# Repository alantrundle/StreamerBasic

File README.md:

# ESP32 Audio Streaming & Playback Platform

An all-in-one **ESP32-based audio platform** providing HTTP streaming, on-device decoding, and multiple audio outputs with a full graphical UI.  
Designed for **ESP32-WROVER (8MB PSRAM)** and intended for use with a **custom PCB (v1.1)** or off-the-shelf modules.

---

## 📸 PCB – Prototype (v1.1)

**Left → Right:**  
Front view with LVGL UI • Player close-up • Angled top view • Rear view with Li-Po battery fitted

> ⚠️ **ESP32-WROVER with 8MB PSRAM is mandatory**  
> Bluetooth Classic (A2DP), audio buffers, and LVGL require PSRAM for stability.

---

## ✨ Key Features

- **Automatic MP3 & AAC codec detection** (header-level)
- **ID3v2 tag parsing**
  - Title, artist, album
  - JPEG album-art decoding
- **Bluetooth A2DP output**
  - Line-out & external sinks
  - Automatic reconnect logic
- **I2S audio output**
  - Developed using PCM5102 DAC
- **Dual-reader PCM ring buffer**
  - Independent A2DP & I2S consumption
- **LVGL graphical UI**
  - Capacitive touch support
  - ST7796 demo included
- **Transport controls**
  - Play / Pause / Stop
  - Next / Previous track

---

## 🧠 Architecture Overview

- HTTP audio streaming
- On-device MP3 / AAC decoding (Helix)
- Shared PCM buffer with dual read pointers
- Parallel audio output to:
  - Bluetooth A2DP
  - I2S DAC
- LVGL UI running primarily from PSRAM
- Designed around **FreeRTOS task separation**, flow-control, and buffer hysteresis

---

## 🖥 TFT Display Pinout (PCB v1.1 – ST7796, SPI)

The PCB v1.1 is wired for a **4″ ST7796 SPI TFT with capacitive touch**, sharing the SPI bus with the SD card.

> ⚠️ TFT and SD **share SPI lines**  
> Separate CS lines are mandatory and handled in firmware.

**4″ TFT Capacitive Touch Display (ST7796)**  
- https://www.aliexpress.com/item/1005006698127763.html

---

### 📌 ESP32 ↔ TFT Connections

| TFT Signal | ESP32 GPIO | ESP32 Pin # | Notes |
|------------|------------|-------------|-------|
| **VCC** | 3.3 V | — | Display power |
| **GND** | GND | — | Ground |
| **CS** | GPIO 33 | **P8** | TFT Chip select |
| **RST** | GPIO 32 | **P7** | TFT reset |
| **DC/RS** | GPIO 27 | **P13** | TFT DC/RS |
| **MOSI** | GPIO 23 | **P37** | VSPI MOSI |
| **SCK** | GPIO 18 | **P30** | VSPI CLK |
| **BL** | GPIO 25 | **P10** | TFT Backlight - PWM capable |
| **MISO** | GPIO 34 | **P37** | VSPI MISO |

---

### ✋ Capacitive Touch Controller (I²C)

(FT6236 / GT911 class controller)

| Touch Signal | ESP32 GPIO | ESP32 Pin # | Notes |
|--------------|------------|-------------|-------|
| **SCL** | GPIO 22 | **P36** | I²C Clock |
| **RST** | GPIO 26 | **P11** | Touch reset |
| **SDA** | GPIO 21 | **P33** | I²C Data |
| **INT** | GPIO 39 | **P4** | Touch interrupt (input-only) |

---

### 💾 SD Card (Shared SPI Bus)

| SD Signal | ESP32 GPIO | ESP32 Pin # | Notes |
|-----------|------------|-------------|-------|
| **VCC** | 3.3 V | — | Power |
| **GND** | GND | — | Ground |
| **CS** | GPIO 5 | **P29** | SD Card Chip Select |
| **SCK** | GPIO 18 | **P30** | Shared VSPI Clock |
| **MOSI** | GPIO 23 | **P37** | Shared VSPI MOSI |
| **MISO** | GPIO 34 | **P5** | Shared VSPI MISO |

---

## 🔌 Expansion Header (PCB v1.1)

Unused GPIOs are exposed via an **Expansion Header** for future peripherals (encoders, buttons, sensors, GPIO).

| Expansion | ESP32 GPIO | ESP32 Pin # | Notes |
|-----------|------------|-------------|-------|
| **3.3V** | 3.3 V | — | Power Output |
| **GND** | GND | — | Ground |
| **SDA** | GPIO 21 | **P33** | I²C SDA (shared with Touch) |
| **SCL** | GPIO 22 | **P36** | I²C SCL (shared with Touch) |
| **SD_CS** | GPIO 5 | **P29** | GPIO if SD not used (strap pin – don’t drive at boot)|
| **GPIO 4** | GPIO 4 | **P26** | GPIO (strap behaviour – keep low/floating at boot)|
| **GPIO 15** | GPIO 15 | **P14** | GPIO (strap pin – must be LOW at boot) |
| **GPIO 19** | GPIO 19 | **P31** | GPIO |
| **GPIO 35** | GPIO 35 | **P6** | Input-only (ADC)|
| **GPIO 36** | GPIO 36 | **P3** | Input-only (ADC)|
| **3.3V** | 3.3 V | — | Power output |
| **GND** | GND | — | Ground |

---

### ⚠️ Electrical & Boot Notes

⚠️ Use with care
GPIO 4, 5 & 15 → boot strap pins (must not be driven during reset)
Must be LOW or floating at boot

GPIO 34 / 39 → input-only, no pullups

❌ Output not possible
GPIO 34–39

---

## ⚠️ Known Issues & Limitations

- **LVGL + Bluetooth + Wi-Fi are extremely DRAM-heavy**
  - LVGL buffers must reside mostly in PSRAM
  - Moving `lvbuf1` to DRAM can crash Wi-Fi + BT
  - Use 4 lines maximum
- **Dual buffering in PSRAM is slower**
  - Trade-off required for system stability
- **Wi-Fi coexistence instability**
  - Occasional crashes under heavy load
- **ESP-IDF versions**
  - Rolled back to **ESP32 core v6.4.0** for stability
  - Newer versions attempt BT sleep → A2DP instability
- **Bluetooth**
  - Seems stable

---

## 🧪 Current Testing Status

- Use stable branch for latest stable

- Use main branch for latest code. 

⚠️ main may be broken if I am in the process of making multi-day changes.

12/01/2026
- added Bluetooth Manager for Sink Devices
- added basic WiFi handler
- changed menu - added icons
- added icon pack to Playback 

---

## 🛠 To-Do

- Plex Media Server integration
- General bug fixes & cleanup
- Ogg Vorbis support
- Improved AAC decoding
- LVGL dual buffering in DRAM (if feasible)

---

## ✅ Pros

- Stable during extended playback
- Robust codec detection
- Clean separation of decode and output paths
- Scales well with PSRAM availability

---

## 📦 Recommended Development Kit (Without PCB)

### ESP32 Module

**ESP32-WROVER (8MB PSRAM + TF Card)**  
- https://www.aliexpress.com/item/32879370278.html

### Display

**4″ TFT Capacitive Touch Display (ST7796)**  
- https://www.aliexpress.com/item/1005006698127763.html

### Audio DAC

**PCM5102 I2S DAC**  
Stereo RCA + headphone / line-out  
- https://www.aliexpress.com/item/1005005352684938.html

---

## 📄 License

**Project status:** Active Development

**License:**  
Free for **personal, educational, and hobbyist use**.

**Commercial use is not permitted without explicit written permission from the author.**  
This includes (but is not limited to) commercial products, services, or redistributed hardware.

If you wish to use this project commercially, please contact the author via GitHub.

---

## 🙌 Acknowledgements

- ESP32 Arduino Core  
- LVGL Graphics Library  
- Helix Audio Codecs  

## 🙌 Development Software
- MacOS 15.5
- Visual Studio Code Version: 1.108.0 (Universal)
- PlatformIO Core Version: 6.1.18·Home 3.4.4
- EEZ Studio Version: 0.24.0
- KiCAD Version: 9.0.6 release build

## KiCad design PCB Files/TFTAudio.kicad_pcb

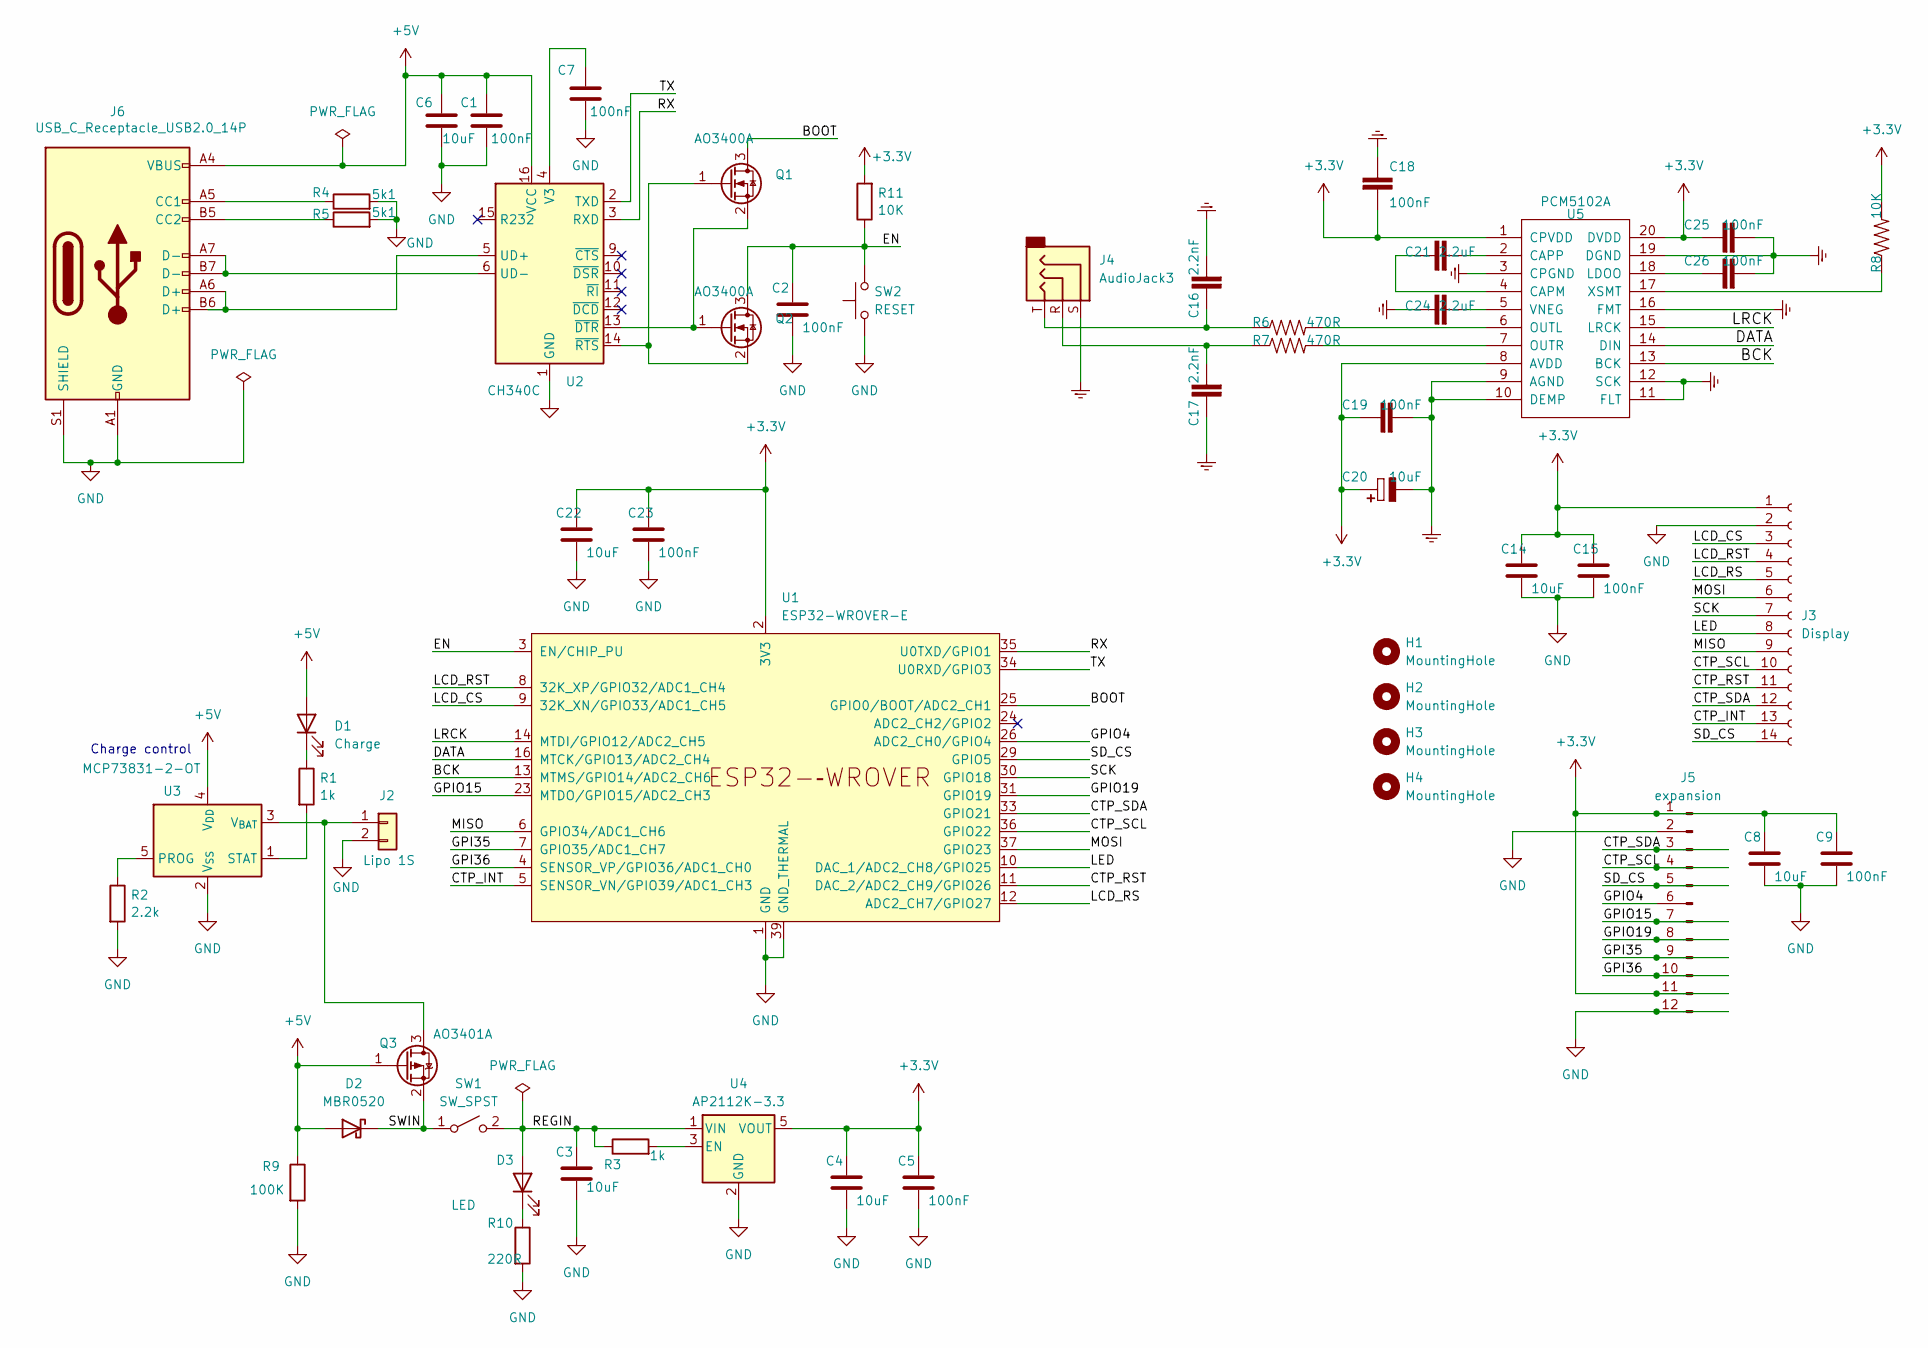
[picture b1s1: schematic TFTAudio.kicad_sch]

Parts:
C1, C2, C5, C7, C9, C15, C18, C19, C23, C25, C26: 100nF; C_0603_1608Metric; LCSC C14663
C3, C4, C6, C8, C14, C20, C22: 10uF; C_0603_1608Metric; LCSC C19702
C16, C17: 2.2nF; C_0603_1608Metric; LCSC C1604
C21, C24: 2.2uF; C_0603_1608Metric; LCSC C23630
D1: Charge; LED_0805_2012Metric; LCSC C84256
D2: MBR0520; D_SOD-123; LCSC C8598
D3: LED; LED_0805_2012Metric; LCSC C2296
H1, H2, H3, H4: MountingHole; MountingHole_3.2mm_M3_ISO14580
J2: Lipo 1S; JST_ZH_S2B-ZR-SM4A-TF_1x02-1MP_P1.50mm_Horizontal
J3: Display; PinSocket_1x14_P2.54mm_Vertical
J4: AudioJack3; Jack_3.5mm_CUI_SJ1-3523N_Horizontal; LCSC C20182914
J5: expansion; PinSocket_1x12_P2.54mm_Vertical
J6: USB_C_Receptacle_USB2.0_14P; USB_C_Receptacle_HRO_TYPE-C-31-M-12; LCSC C165948
Q1, Q2: AO3400A; SOT-23; LCSC C20917
Q3: AO3401A; Package_TO_SOT_SMD; LCSC C15127
R1, R3: 1k; R_0603_1608Metric; LCSC C21190
R2: 2.2k; R_0603_1608Metric; LCSC C4190
R4, R5: 5k1; R_0603_1608Metric; LCSC C23186
R6, R7: 470R; R_0603_1608Metric; LCSC C23179
R8, R11: 10K; R_0603_1608Metric; LCSC C25804
R9: 100K; R_0603_1608Metric; LCSC C25803
R10: 220R; R_0603_1608Metric; LCSC C22962
SW1: SW_SPST; SW_Slide_SPDT_Angled_CK_OS102011MA1Q; LCSC C226259
SW2: RESET; SW_SPST_EVQP7C; LCSC C388883
U1: ESP32-WROVER-E; LCSC C701342
U2: CH340C; SOIC-16_3.9x9.9mm_P1.27mm; LCSC C84681
U3: MCP73831-2-OT; SOT-23-5; LCSC C424093
U4: AP2112K-3.3; SOT-23-5; LCSC C51118
U5: PCM5102A; TSSOP-20_4.4x6.5mm_P0.65mm; LCSC C107671

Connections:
+3.3V: C4.1, C5.1, C8.1, C9.1, C14.1, C15.1, C18.2, C19.1, C20.1 (+), C22.1, C23.1, C25.1, J3.1, J5.1, J5.11, R8.2, R11.2, U1.2 (3V3), U4.5 (VOUT), U5.1 (CPVDD), U5.8 (AVDD), U5.20 (DVDD)
+5V: C1.1, C6.1, D1.2 (A), D2.2 (A), J6.A4 (VBUS), J6.A9 (VBUS), J6.B4 (VBUS), J6.B9 (VBUS), Q3.1 (G), R9.1, U2.16 (VCC), U3.4 (V_{DD})
/BCK: U1.13 (MTMS/GPIO14/ADC2_CH6), U5.13 (BCK)
/BOOT: Q1.3 (D), U1.25 (GPIO0/BOOT/ADC2_CH1)
/CTP_INT: J3.13, U1.5 (SENSOR_VN/GPIO39/ADC1_CH3)
/CTP_RST: J3.11, U1.11 (DAC_2/ADC2_CH9/GPIO26)
/CTP_SCL: J3.10, J5.4, U1.36 (GPIO22)
/CTP_SDA: J3.12, J5.3, U1.33 (GPIO21)
/DATA: U1.16 (MTCK/GPIO13/ADC2_CH4), U5.14 (DIN)
/EN: C2.1, Q2.3 (D), R11.1, SW2.2, U1.3 (EN/CHIP_PU)
/GPI35: J5.9, U1.7 (GPIO35/ADC1_CH7)
/GPI36: J5.10, U1.4 (SENSOR_VP/GPIO36/ADC1_CH0)
/GPIO4: J5.6, U1.26 (ADC2_CH0/GPIO4)
/GPIO15: J5.7, U1.23 (MTDO/GPIO15/ADC2_CH3)
/GPIO19: J5.8, U1.31 (GPIO19)
/LCD_CS: J3.3, U1.9 (32K_XN/GPIO33/ADC1_CH5)
/LCD_RS: J3.5, U1.12 (ADC2_CH7/GPIO27)
/LCD_RST: J3.4, U1.8 (32K_XP/GPIO32/ADC1_CH4)
/LED: J3.8, U1.10 (DAC_1/ADC2_CH8/GPIO25)
/LRCK: U1.14 (MTDI/GPIO12/ADC2_CH5), U5.15 (LRCK)
/MISO: J3.9, U1.6 (GPIO34/ADC1_CH6)
/MOSI: J3.6, U1.37 (GPIO23)
/REGIN: C3.1, D3.2 (A), R3.1, SW1.2 (B), U4.1 (VIN)
/RX: U1.35 (U0TXD/GPIO1), U2.3 (RXD)
/SCK: J3.7, U1.30 (GPIO18)
/SD_CS: J3.14, J5.5, U1.29 (GPIO5)
/SWIN: D2.1 (K), Q3.2 (S), SW1.1 (A)
/TX: U1.34 (U0RXD/GPIO3), U2.2 (TXD)
GND: C1.2, C2.2, C3.2, C4.2, C5.2, C6.2, C7.2, C8.2, C9.2, C14.2, C15.2, C16.2, C17.1, C18.1, C19.2, C20.2 (-), C22.2, C23.2, C24.1, C25.2, C26.2, J2.2, J3.2, J4.S, J5.2, J5.12, J6.A1 (GND), J6.A12 (GND), J6.B1 (GND), J6.B12 (GND), J6.S1 (SHIELD), R2.2, R4.2, R5.2, R9.2, R10.2, SW2.1, U1.1 (GND), U1.15 (GND), U1.38 (GND), U1.39 (GND_THERMAL), U2.1 (GND), U3.2 (V_{SS}), U4.2 (GND), U5.3 (CPGND), U5.9 (AGND), U5.10 (DEMP), U5.11 (FLT), U5.12 (SCK), U5.16 (FMT), U5.19 (DGND)
unnamed: C16.1, J4.T, R6.1
unnamed: C17.2, J4.R, R7.1
unnamed: D1.1 (K), R1.1
unnamed: D3.1 (K), R10.1
unnamed: J2.1, Q3.3 (D), U3.3 (V_{BAT})
unnamed: J6.A5 (CC1), R4.1
unnamed: J6.B5 (CC2), R5.1
unnamed: Q1.1 (G), Q2.2 (S), U2.14 (~RTS)
unnamed: Q1.2 (S), Q2.1 (G), U2.13 (~DTR)
unnamed: J6.A6 (D+), J6.B6 (D+), U2.5 (UD+)
unnamed: J6.A7 (D-), J6.B7 (D-), U2.6 (UD-)
unnamed: C7.1, U2.4 (V3)
unnamed: R2.1, U3.5 (PROG)
unnamed: R1.2, U3.1 (STAT)
unnamed: R3.2, U4.3 (EN)
unnamed: C21.1, U5.4 (CAPM)
unnamed: C21.2, U5.2 (CAPP)
unnamed: C26.1, U5.18 (LDOO)
unnamed: R6.2, U5.6 (OUTL)
unnamed: R7.2, U5.7 (OUTR)
unnamed: C24.2, U5.5 (VNEG)
unnamed: R8.1, U5.17 (XSMT)

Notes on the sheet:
Charge control

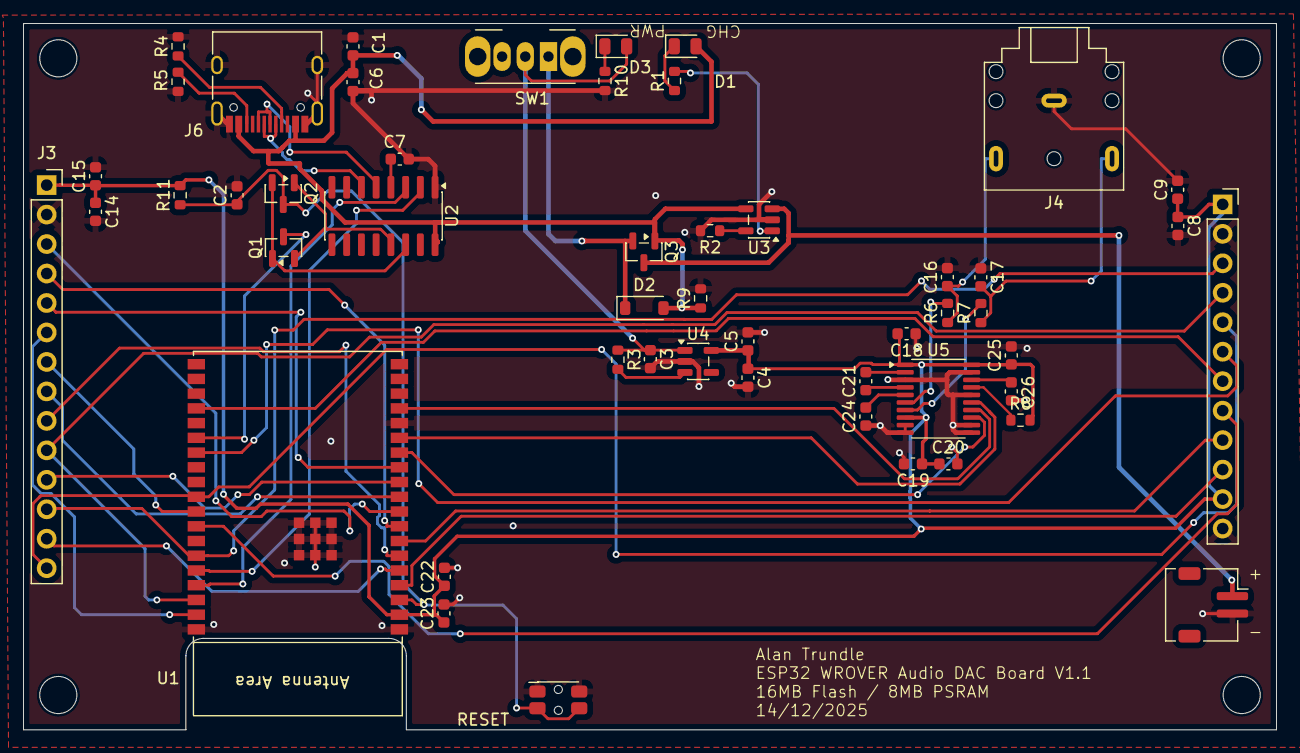
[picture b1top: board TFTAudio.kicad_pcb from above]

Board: 2 copper layers, 108.0 x 60.9 mm, 55 parts (0 on the bottom side), 51 nets.

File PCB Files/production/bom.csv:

Designator,Footprint,Quantity,Value,LCSC Part #
"C1, C15, C18, C19, C2, C23, C25, C26, C5, C7, C9",0603,11,100nF,C14663
"C14, C20, C22, C3, C4, C6, C8",0603,7,10uF,C19702
"C16, C17",0603,2,2.2nF,C1604
"C21, C24",0603,2,2.2uF,C23630
D1,0805,1,Charge,C84256
D2,D_SOD-123,1,MBR0520,C8598 
D3,0805,1,LED,C2296
"H1, H2, H3, H4",MountingHole_3.2mm_M3_ISO14580,4,MountingHole,
J2,JST_ZH_S2B-ZR-SM4A-TF_1x02-1MP_P1.50mm_Horizontal,1,Lipo 1S,
J3,PinSocket_1x14_P2.54mm_Vertical,1,Display,
J4,Jack_3.5mm_CUI_SJ1-3523N_Horizontal,1,AudioJack3,C20182914 
J5,PinSocket_1x12_P2.54mm_Vertical,1,expansion,
J6,USB_C_Receptacle_HRO_TYPE-C-31-M-12,1,USB_C_Receptacle_USB2.0_14P,C165948
"Q1, Q2",SOT-23,2,AO3400A,C20917
Q3,SOT-23,1,AO3401A,C15127
"R1, R3",0603,2,1k,C21190
R10,0603,1,220R,C22962
"R11, R8",0603,2,10K,C25804
R2,0603,1,2.2k,C4190
"R4, R5",0603,2,5k1,C23186 
"R6, R7",0603,2,470R,C23179
R9,0603,1,100K,C25803
SW1,SW_Slide_SPDT_Angled_CK_OS102011MA1Q,1,SW_SPST,C226259
SW2,SW_SPST_EVQP7C,1,RESET,C388883
U1,ESP32-WROVER-E,1,ESP32-WROVER-E,C701342
U2,SOIC-16_3.9x9.9mm_P1.27mm,1,CH340C,C84681
U3,SOT-23-5,1,MCP73831-2-OT,C424093
U4,SOT-23-5,1,AP2112K-3.3,C51118
U5,TSSOP-20_4.4x6.5mm_P0.65mm,1,PCM5102A,C107671

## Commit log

2025-11-27 Working stable
2025-11-27 added ID3 Support to LVGL
2025-11-28 added player controls - enabled on WIFI STABLE
2025-11-28 minor auto advance bug fix
2025-11-29 introduced A2DP. Major bugs BT Stack
2025-11-29 A2DP Working & auto reconnect added (pre debug)
2025-11-29 changes to task priorities
2025-11-29 minor changes to decodeTask
2025-11-29 Stable release
2025-11-29 minor changes A2DP Working
2025-11-30 working [Stable]
2025-11-30 stable - pre release
2025-11-30 stable 20251130 AM
2025-11-30 added PCM priming & A2DP output stability
2025-12-01 added bt+wifi sleep to disabled
2025-12-01 chanhed LVGL settings
2025-12-01 clearPCM bug fix
2025-12-01 added NV storage for A2DP auto connect + other minor bug fixes
2025-12-01 delay fixes HTTP
2025-12-01 minor changes to BT scan CB
2025-12-01 idv3 bug fix v2 + lvgl fixes
2025-12-01 fixed IDv3 + header detection - large ID3 tags
2025-12-02 pm buffer fixes - crashing fixed (testing)
2025-12-02 running 24 hour soak test
2025-12-02 BT sleep issues debugging
2025-12-02 update to readme
2025-12-02 strcpy work to be done - bugs
2025-12-02 fixed strcpy crash - testing to be done
2025-12-03 added JPEG album art support + minor bug fixed. Pre soak test
2025-12-03 downgraded ESP32 firmware
2025-12-03 i2s DMA changes
2025-12-06 Added PCB Files
2025-12-06 added de-coupling to PCB schematic
2025-12-07 minor changes to fix DMA issues.
2025-12-07 [Stable]
2025-12-07 uodated PCB files - added PCM5102
2025-12-08 Mark R Commit - PCB help
2025-12-12 pcb - finished draft 1.0
2025-12-12 1st draft PCB
2025-12-12 PCB 2nd draft
2025-12-13 PCB Draft 3
2025-12-13 PCB draft 4
2025-12-13 PCB Draft 5
2025-12-14 PCB Final Draft
2025-12-14 Submitted PCB
2025-12-14 Post submit tweaks
2025-12-15 production
2025-12-15 Production PCB v1.1
2025-12-15 Current Working
2025-12-15 Initial commit (clean reset)
2025-12-15 Sequencing fixes AudioCore
2025-12-15 changed delays in HSE and AC to provide more spare CPU time.
2025-12-15 changed refresh rate LVGL
2025-12-15 Altered PCM buffer size for stability + fixed PCM draining issues - Audio Side
2025-12-15 minor logic flow bug fixes
2025-12-15 production - Stable V1.1 - headphones out of range fix
2025-12-15 V1.3 stable - earphones out of range
2025-12-21 minor improvements to AC and HSE
2025-12-21 minor fixes - AC dropped packets [STABLE]
2025-12-22 idv3 fixes - set packet size to 256 [STABLE]
2026-01-03 added images to GH
2026-01-03 README update
2026-01-03 Readme update licence
2026-01-03 alteraitons to IDv3 tag. Album art
2026-01-03 Readme changes
2026-01-03 added images
2026-01-09 stable
2026-01-09 minor changes to platformio
2026-01-10 added i2s/a2dp icons
2026-01-10 added id3 icons
2026-01-10 changes to README
2026-01-10 added image assets
2026-01-12 menu updated - added icons
2026-01-12 changes to Readme.MD
2026-01-12 changes to Readme - added pinout for PCB V1.1
2026-01-12 readme bug
2026-01-12 readme.MD changes
2026-01-12 added BT management
2026-01-12 fixed bluetooth maangement
2026-01-12 minor display changes [Player]
2026-01-12 added basic WiFi managment
2026-01-12 minor changes to playlist
2026-01-12 Readme.MD changes to Software section
